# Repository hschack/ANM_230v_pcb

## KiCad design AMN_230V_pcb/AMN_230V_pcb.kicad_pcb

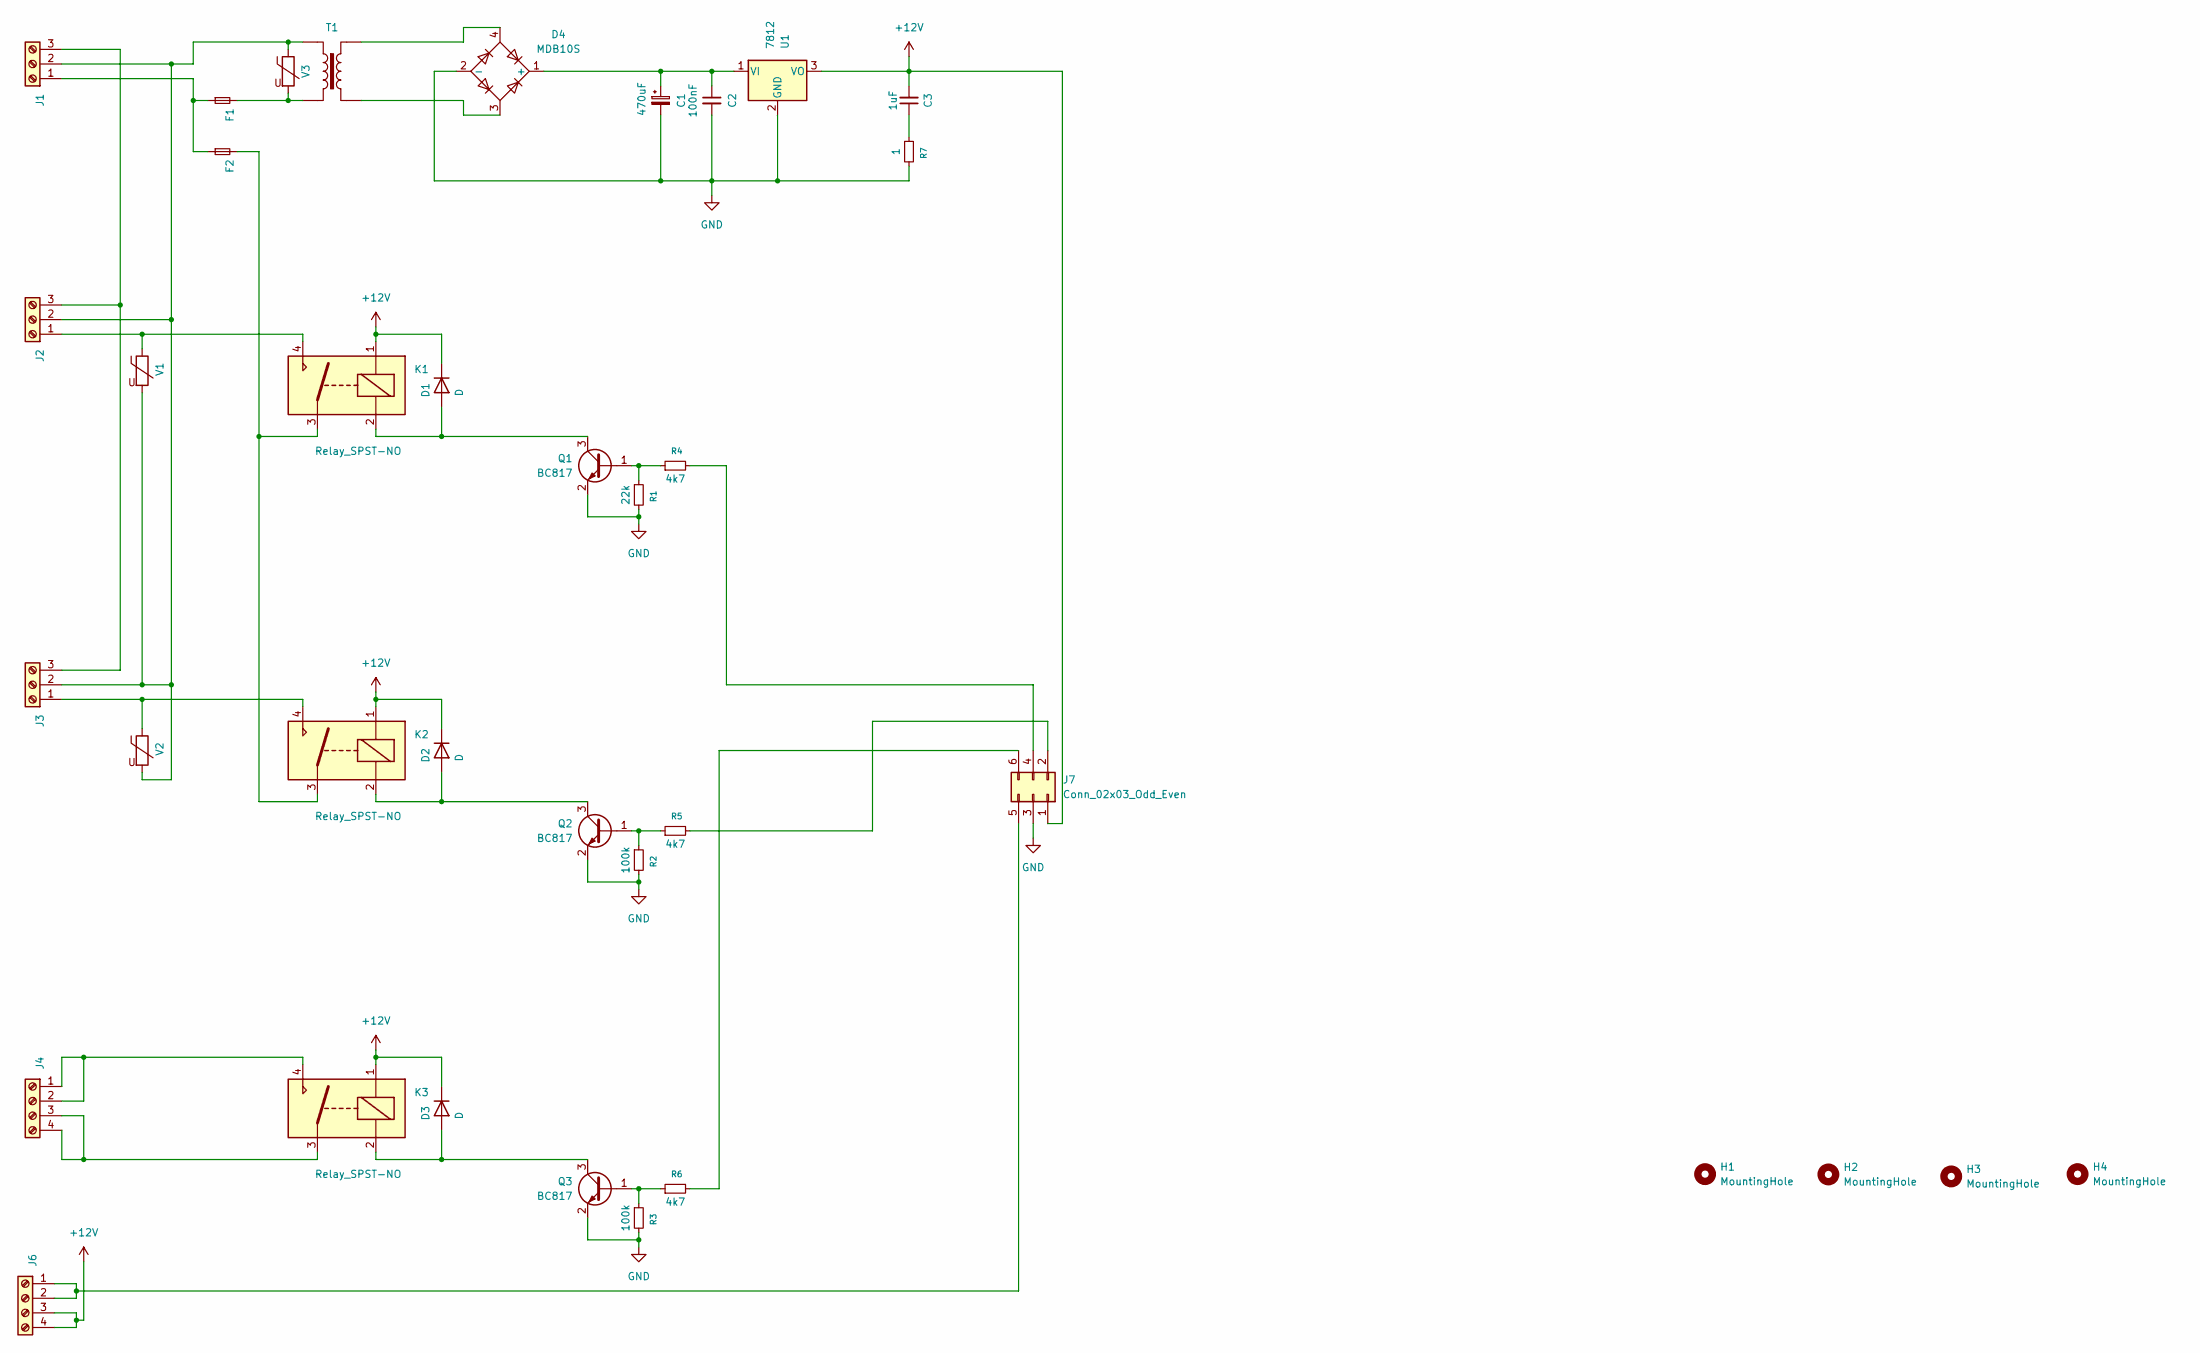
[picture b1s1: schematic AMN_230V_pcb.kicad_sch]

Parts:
C1: 470uF; CP_Elec_10x10.5
C2: 100nF; C_0603_1608Metric
C3: 1uF; C_0603_1608Metric
D1, D2, D3: D; D_SMA
D4: MDB10S; TSSOP-4_4.4x5mm_P4mm
F1, F2: Fuse_Small; Fuse_Littelfuse_372_D8.50mm
H1, H2, H3, H4: MountingHole; MountingHole_3.5mm
J1, J2, J3: Screw_Terminal_01x03; PhoenixContact_MSTBVA_2,5_3-G-5,08_1x03_P5.08mm_Vertical
J4, J6: Screw_Terminal_01x04; PhoenixContact_MCV_1,5_4-G-3.5_1x04_P3.50mm_Vertical
J7: Conn_02x03_Odd_Even; PinSocket_2x03_P2.54mm_Vertical
K1, K2, K3: Relay_SPST-NO; Relay_SPST_TE_PCN-1xxD3MHZ
Q1, Q2, Q3: BC817; SOT-23
R1: 22k; R_0603_1608Metric
R2, R3: 100k; R_0603_1608Metric
R4, R5, R6: 4k7; R_0603_1608Metric
R7: 1; R_0603_1608Metric
T1: TRANSF1; VB-1,5_1_6
U1: 7812; TO-252-2
V1, V2, V3: Varistor; RV_Disc_D12mm_W3.9mm_P7.5mm

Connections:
+12V: C3.2, D1.1 (K), D2.1 (K), D3.1 (K), J6.3, J6.4, J7.1, K1.1, K2.1, K3.1, U1.3 (VO)
GND: C1.2, C2.2, D4.2 (-), J7.3, Q1.2 (E), Q2.2 (E), Q3.2 (E), R1.2, R2.2, R3.2, R7.2, U1.2 (GND)
unnamed: C3.1, R7.1
unnamed: D1.2 (A), K1.2, Q1.3 (C)
unnamed: D2.2 (A), K2.2, Q2.3 (C)
unnamed: D3.2 (A), K3.2, Q3.3 (C)
unnamed: C1.1, C2.1, D4.1 (+), U1.1 (VI)
unnamed: D4.3, T1.3
unnamed: D4.4, T1.4
unnamed: F1.2, T1.2, V3.2
unnamed: F2.2, K1.3, K2.3
unnamed: F1.1, F2.1, J1.1
unnamed: J1.2, J2.2, J3.2, T1.1, V1.2, V2.2, V3.1
unnamed: J1.3, J2.3, J3.3
unnamed: J2.1, K1.4, V1.1
unnamed: J3.1, K2.4, V2.1
unnamed: J4.1, J4.2, K3.4
unnamed: J4.3, J4.4, K3.3
unnamed: J6.1, J6.2, J7.5
unnamed: J7.2, R5.2
unnamed: J7.4, R4.2
unnamed: J7.6, R6.2
unnamed: Q1.1 (B), R1.1, R4.1
unnamed: Q2.1 (B), R2.1, R5.1
unnamed: Q3.1 (B), R3.1, R6.1

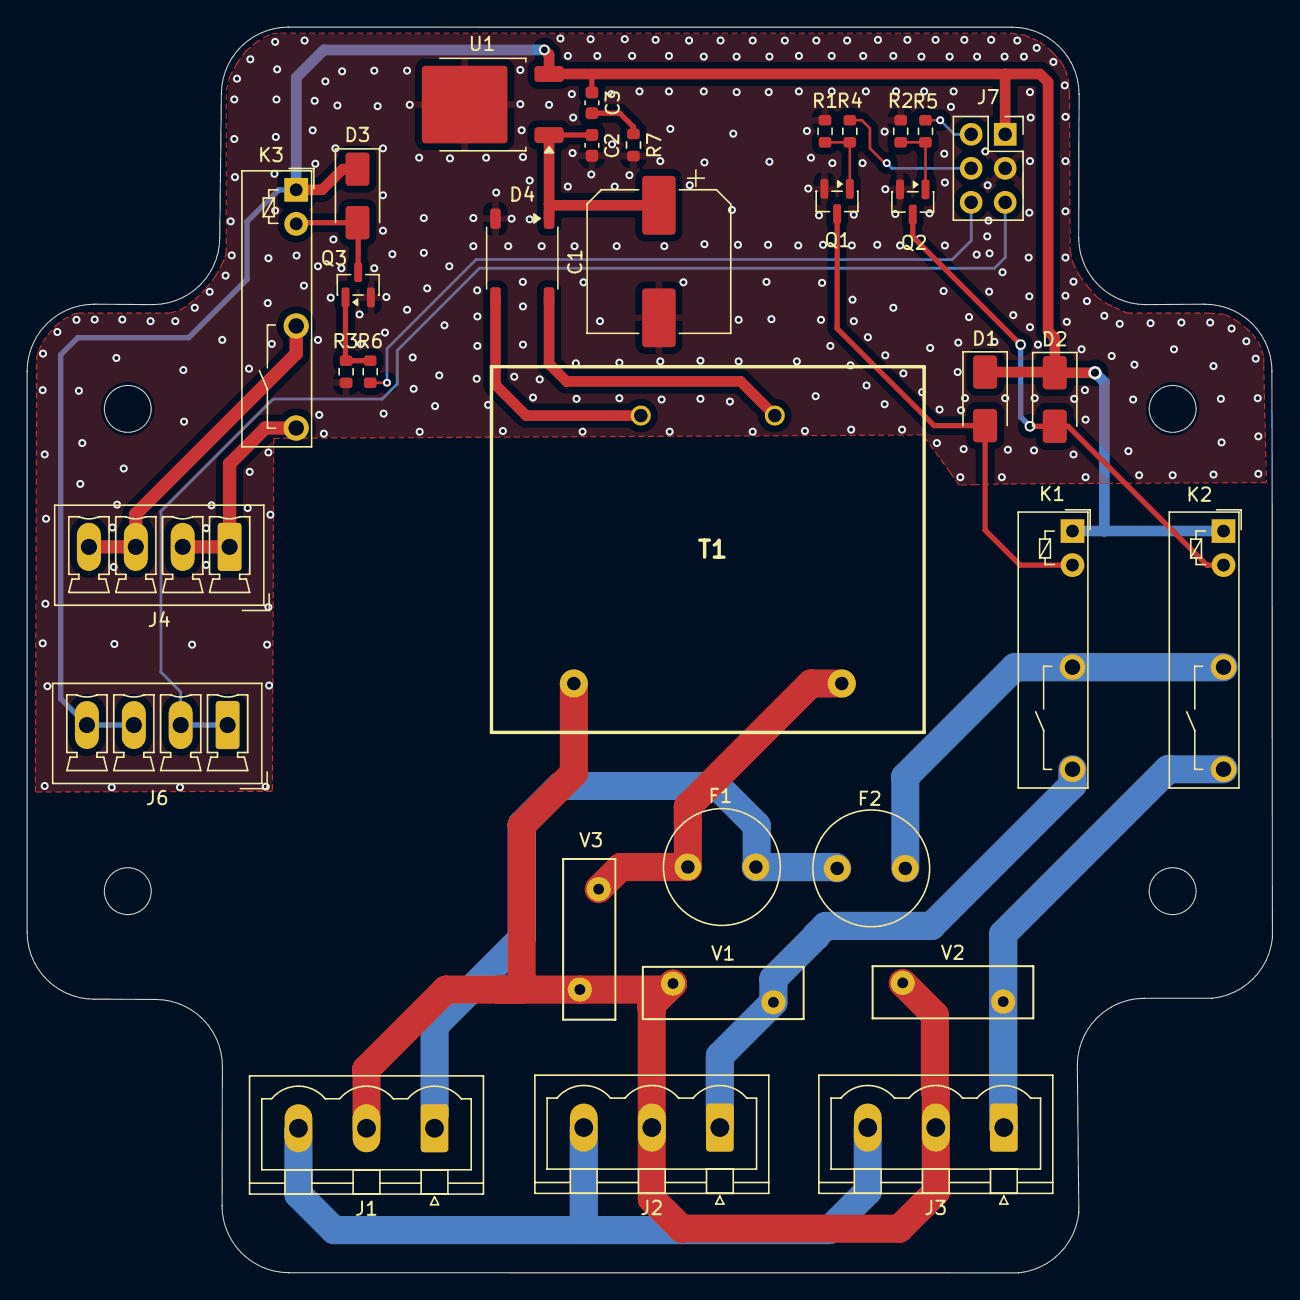
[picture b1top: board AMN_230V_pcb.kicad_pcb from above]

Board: 2 copper layers, 93.0 x 93.0 mm, 37 parts (0 on the bottom side), 25 nets.
